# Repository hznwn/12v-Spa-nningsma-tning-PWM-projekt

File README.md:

The files contained within this project were created for an electric car conversion project formed within the "Project Work in Electrical Engineering" course at Uppsala University. The course is a part of the "Master's Programme in Electrical Engineering" and took place between the fall of 2022 and spring 2023.

Volvo group donated 3 cars to Uppsala University in order to remove the combustion engines and instead replace them with electric motors. 
More details about the course and program can be found below. 

In order to complete the goals of the car conversion project, a total of twelve 12-volt batteries were placed in the trunk in order to power the electric motors. The batteries were then connected in series to achieve a total of 144-volts. 

The files found within this github project pertain to the measurement of voltage across each of the 12-volt batteries.
Measuring the voltage of 12 individual batteries, at 12 V with different relative potential levels, can provide critical information when it comes to troubleshooting and solving potential problems. Voltage level can indicate whether a circuit is supplied with too much or too little voltage. In addition, it is also possible to identify which individual component may be the cause of the problem based on the voltage drop (if it has a larger or smaller voltage drop than expected.

The solution presented within the LTSpice and KiKad files was required as the voltage of all the batteries must be measured simultaneously, even when they have different "grounds" (common). Additionally, in order to gather the signals and data log and store the values, a National Instruments MyRIO was used. MyRIO is a real-time embedded evaluation board, and only supports measurements between 0-5V, so many adjustments were needed to safely ensure it could read and accept the signals from the batteries. 

All files, with exception to the group report, and labview files was created solely by hznwn. 
The labview files was created by hzwnwm and HKlasmanGustafsson.

Big thanks to all involved in the project as well. 

More details:
Kursplan för Projektarbete i elektroteknik:
https://www.uu.se/utbildning/utbildningar/selma/kursplan?kpid=39132&type=1

Civilingenjörsprogrammet i elektroteknik:
https://www.uu.se/utbildning/utbildningar/selma/program/?pKod=TEL2Y

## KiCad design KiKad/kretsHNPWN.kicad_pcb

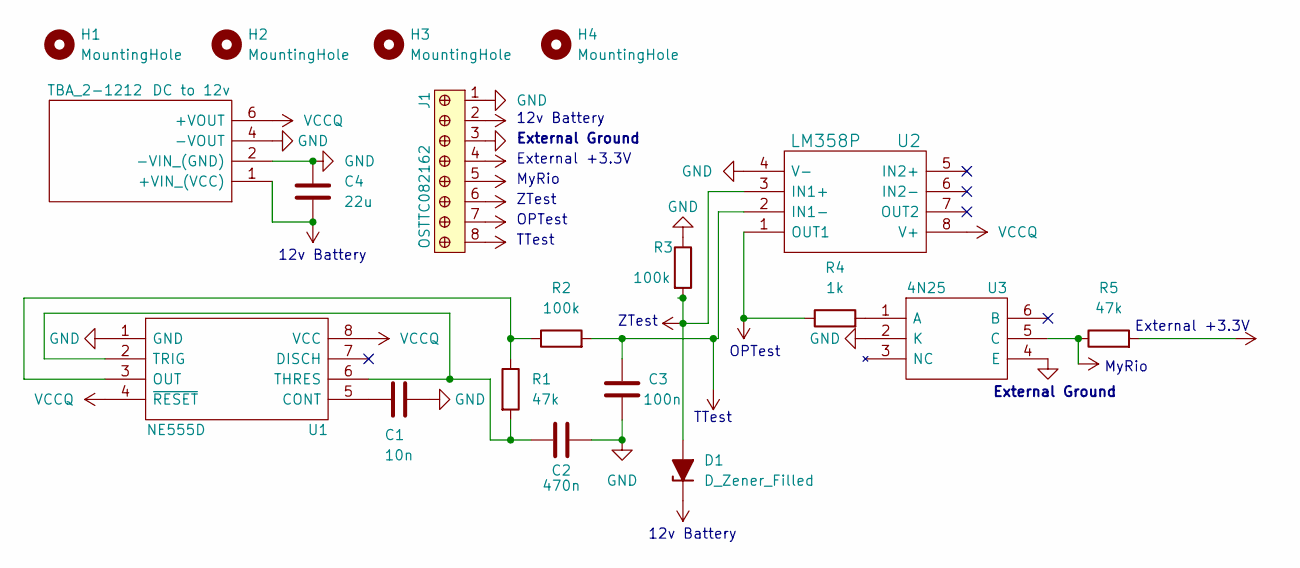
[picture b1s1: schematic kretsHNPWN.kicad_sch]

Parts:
C1: 10n; C0603
C2: 470n; CP_Radial_Tantal_D4.5mm_P5.00mm
C3: 100n; CP_Radial_Tantal_D4.5mm_P5.00mm
C4: 22u; CAPC2012X145N
D1: D_Zener_Filled; D_DO-41_SOD81_P7.62mm_Horizontal
H1, H2, H3, H4: MountingHole; MountingHole_3.2mm_M3
J1: OSTTC082162; Term_Block_1x8_P5.08mm; MPN OSTTC082162; Digi-Key_PN ED2615-ND
R1, R5: 47k; R_Axial_DIN0204_L3.6mm_D1.6mm_P7.62mm_Horizontal
R2, R3: 100k; R_Axial_DIN0204_L3.6mm_D1.6mm_P7.62mm_Horizontal
R4: 1k; R_Axial_DIN0204_L3.6mm_D1.6mm_P7.62mm_Horizontal
TBA_2-1212: DC to 12v; TBA22412; PARTREV April 19, 2021; Mouser Part Number 495-TBA2-1212
U1: NE555D; SOIC127P600X175-8N; Manufacturer_Part_Number NE555DR; Mouser Part Number 595-NE555DR
U2: LM358P; DIP794W53P254L959H508Q8N; MPN LM358P; Digi-Key_PN 296-1395-5-ND
U3: 4N25; DIP762W60P254L712H480Q6N; Manufacturer_Part_Number 4N25; Mouser Part Number 78-4N25

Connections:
+3.3V: J1.4, R5.2
GND: C1.1, C2.2, C3.2, C4.2, J1.1, R3.1, TBA_2-1212.2 (-VIN_(GND)), TBA_2-1212.4 (-VOUT), U1.1 (GND), U2.4 (V-), U3.2 (K)
GND2: J1.3, U3.4 (E)
unnamed: C1.2, U1.5 (CONT)
unnamed: C2.1, R1.2, U1.2 (TRIG), U1.6 (THRES)
unnamed: R1.1, R2.1, U1.3 (OUT)
unnamed: R4.2, U3.1 (A)
VAA: D1.2 (A), J1.6, R3.2, U2.3 (IN1+)
VBUS: J1.5, R5.1, U3.5 (C)
VCC: C4.1, D1.1 (K), J1.2, TBA_2-1212.1 (+VIN_(VCC))
VCCQ: TBA_2-1212.6 (+VOUT), U1.4 (~RESET), U1.8 (VCC), U2.8 (V+)
VD: J1.7, R4.1, U2.1 (OUT1)
VDDF: C3.1, J1.8, R2.2, U2.2 (IN1-)

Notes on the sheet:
OPTest
External +3.3V
12v Battery
External Ground
TTest
MyRio
ZTest

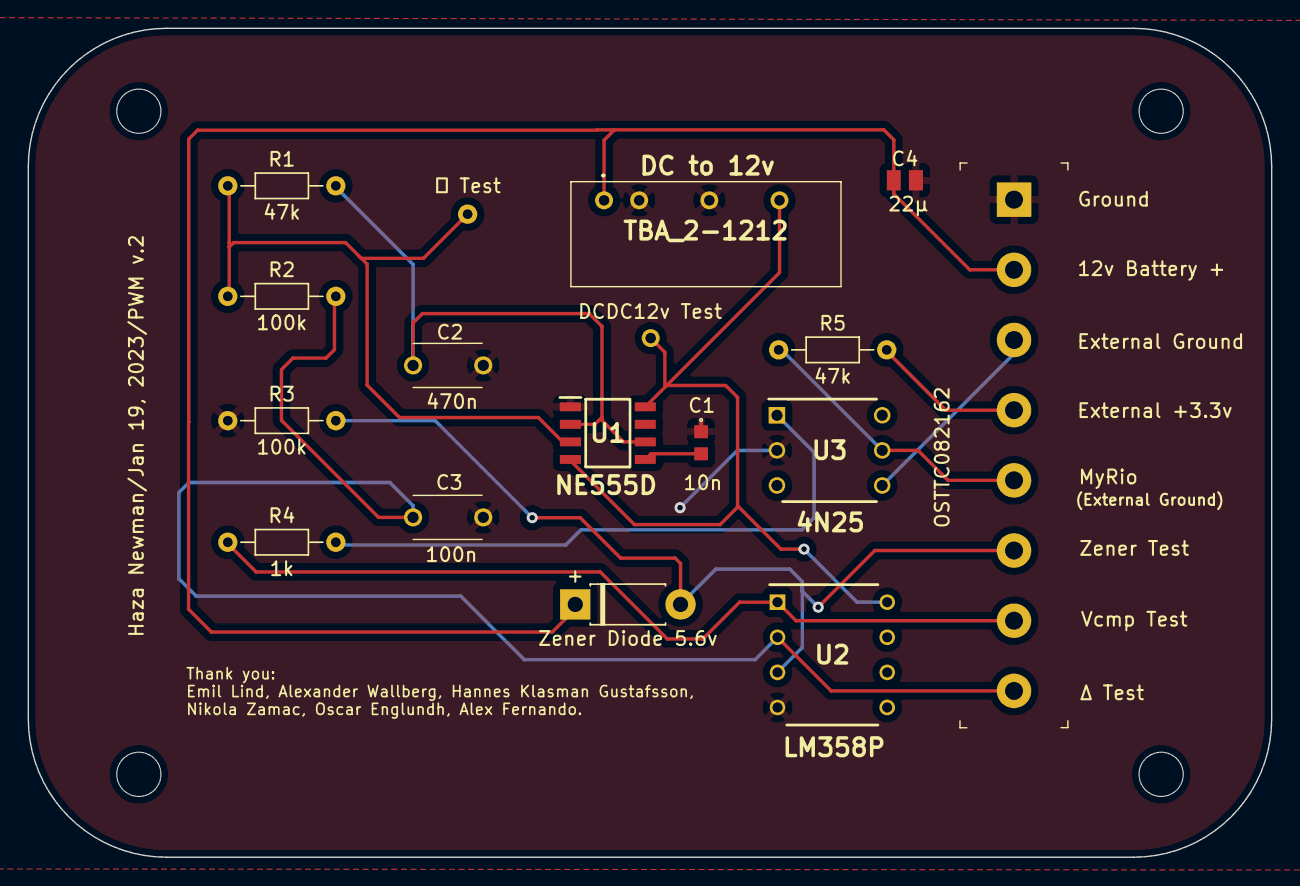
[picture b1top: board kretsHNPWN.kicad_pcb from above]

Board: 2 copper layers, 90.0 x 60.0 mm, 19 parts (0 on the bottom side), 13 nets.
